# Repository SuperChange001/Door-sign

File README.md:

# Door Sign Design
---
## Preview

## Folder Structure
```bash
├── README.md
├── door-sign
│   ├── bom
│   │   ├── Parts_ordering_digikey.xlsx
│   │   └── ibom.html
│   ├── door-sign.kicad_pcb
│   ├── door-sign.kicad_prl
│   ├── door-sign.kicad_pro
│   ├── door-sign.kicad_sch
│   ├── fp-lib-table
│   ├── schematic.pdf
│   └── sym-lib-table
├── images
│   └── preview.jpg
└── libs
```

## Todo
- [x] schematic
- [x] pcb
- [x] check
- [x] bom
- [x] order
    - [x] pcb
    - [x] components
- [x] test
    - found one error that the direction of the switch is is not as intuative as it should be, and this is fixed in in v1.0
    - found the potentiometer is not in the center of the rectangle, and this is fixed in v1.0
    - add version number to the pcb
- [x] revision for 1.0
    - [x] add version number to the pcb
    - [x] fix the direction of the switch
    - [x] fix the position of the potentiometer

## Acknowledgement
Thanks, Peter (I should add his GitHub account here), for the idea and the perfect layout of the door sign.

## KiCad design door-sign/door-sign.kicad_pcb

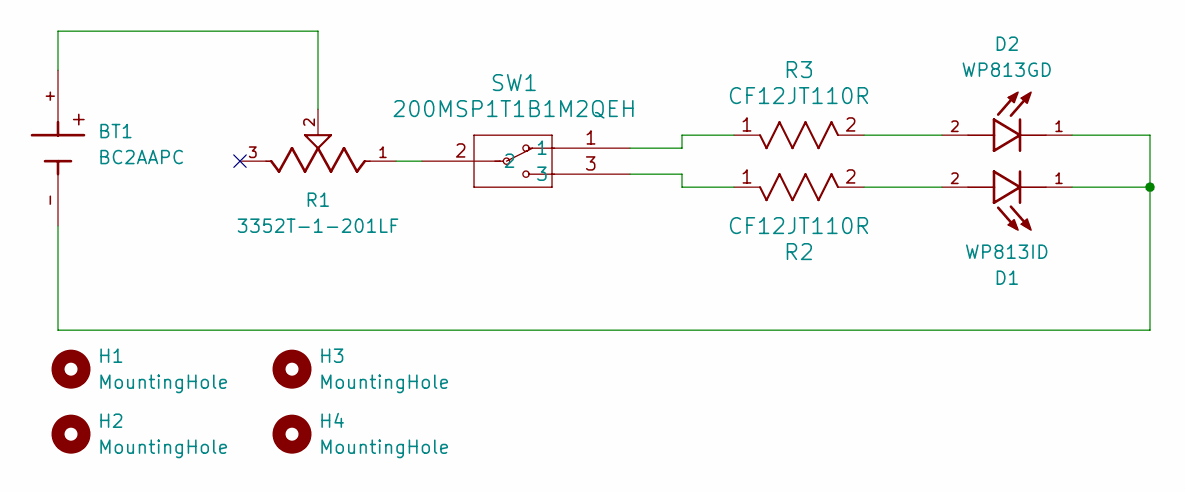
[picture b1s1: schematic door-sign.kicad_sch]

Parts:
BT1: BC2AAPC; BAT_BC2AAPC; PARTREV M
D1: WP813ID; LEDRD254W57D1100H1450; PARTREV V.9B
D2: WP813GD; LEDRD254W57D1100H1450; PARTREV V.9B
H1, H2, H3, H4: MountingHole; MountingHole_5mm
R1: 3352T-1-201LF; TRIM_3352T-1-501LF; PARTREV 08/19
R2, R3: CF12JT110R; STA_CF12_STP
SW1: 200MSP1T1B1M2QEH; 200MSP1T1B1M2QEH_EWI

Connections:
unnamed: BT1.+, R1.2
unnamed: BT1.-, D1.1, D2.1
unnamed: D1.2, R2.2
unnamed: D2.2, R3.2
unnamed: R1.1, SW1.2
unnamed: R2.1, SW1.3
unnamed: R3.1, SW1.1

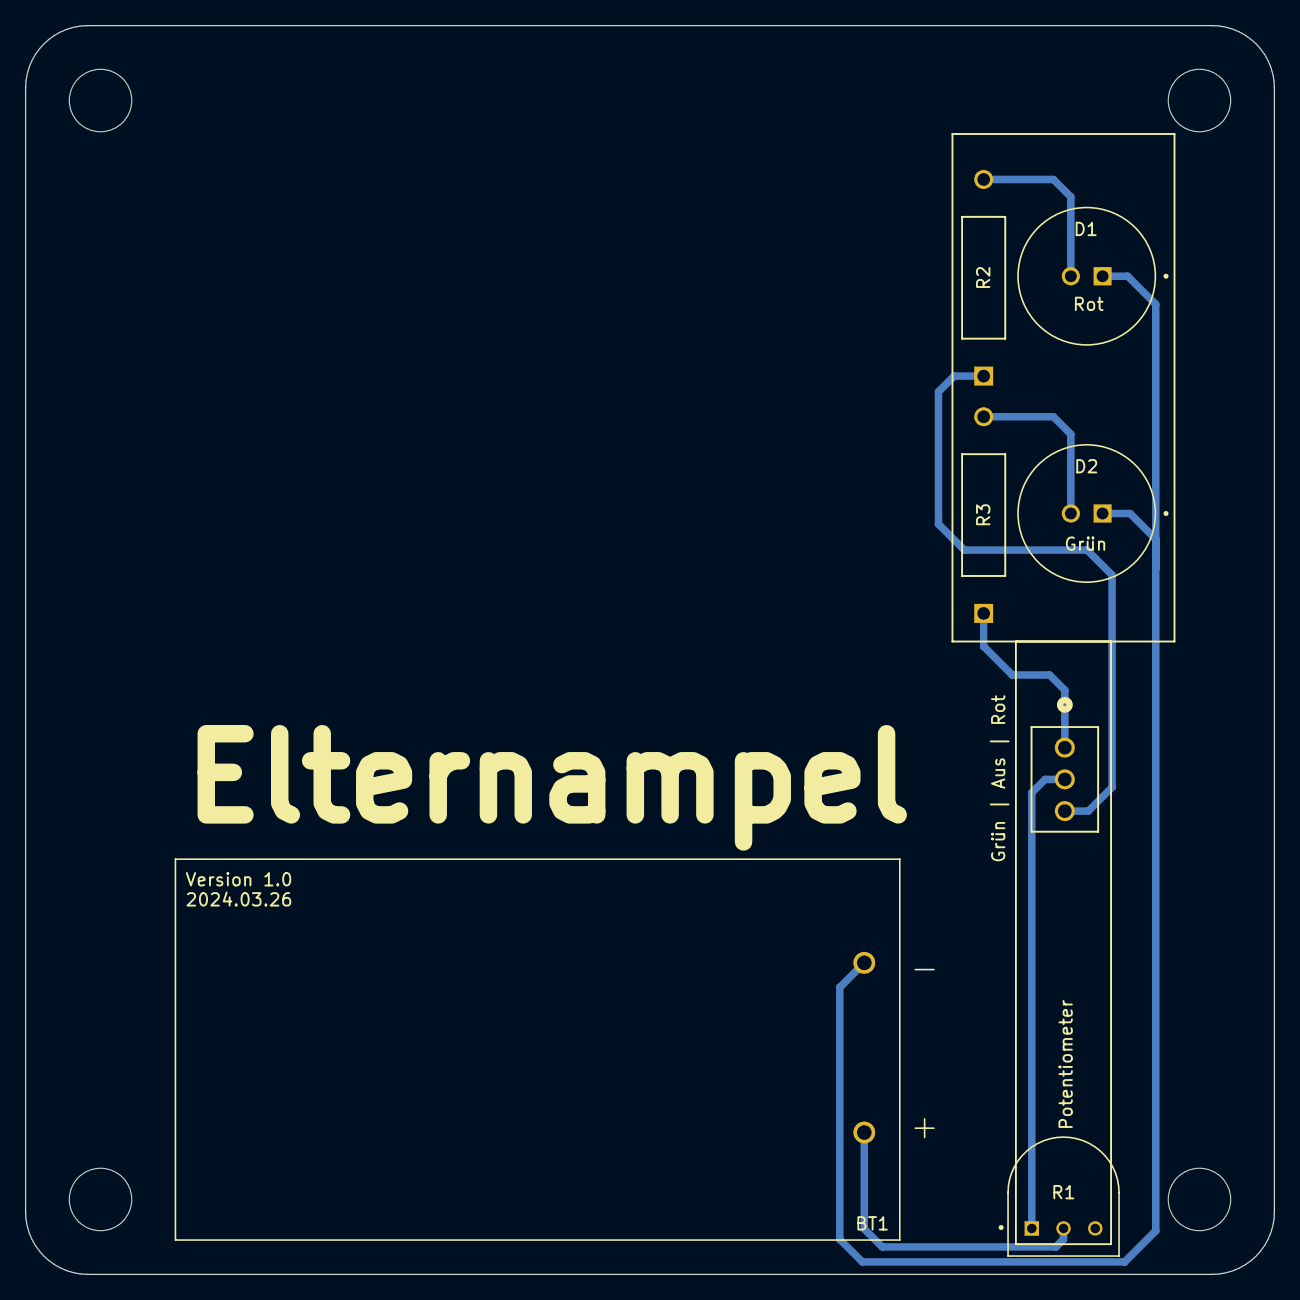
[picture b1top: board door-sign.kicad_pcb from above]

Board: 2 copper layers, 100.0 x 100.0 mm, 11 parts (0 on the bottom side), 7 nets.

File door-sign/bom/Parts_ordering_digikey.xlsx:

Index | Quantity | Part Number | Manufacturer Part Number | Description | Customer Reference | Available | Backorder | Unit Price | Extended Price EUR
1 | 20 | BC2AAPC-ND | BC2AAPC | BATTERY HOLDER AA 2 CELL PC PIN |  | 20 | 0 | 1.28900 | 25.78
2 | 50 | CF12JT100RCT-ND | CF12JT100R | RES 100 OHM 5% 1/2W AXIAL |  | 50 | 0 | 0.03580 | 1.79
3 | 20 | WP813ID-ND | WP813ID | LED RED DIFFUSED 10MM T/H |  | 20 | 0 | 0.23900 | 4.78
4 | 20 | 754-1898-ND | WP813GD | LED GREEN DIFFUSED 10MM T/H |  | 20 | 0 | 0.26200 | 5.24
5 | 20 | EG2447-ND | 200MSP1T1B1M2QEH | SWITCH TOGGLE SPDT 3A 120V |  | 20 | 0 | 2.46200 | 49.24
6 | 20 | 3352T-201LF-ND | 3352T-1-201LF | THUMBWHEEL POT 200 OHM 0.5W TOP |  | 20 | 0 | 2.74200 | 54.84

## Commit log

2024-02-18 middle stage, need a green led
2024-02-19 components done
2024-02-19 add readme
2024-03-02 changed one symbol
2024-03-02 changed one footprint
2024-03-02 changed design
2024-03-02 changed the preview
2024-03-02 add documentation
2024-03-02 erc error free
2024-03-02 done
2024-03-02 update image
2024-03-02 moved parts a little bit
2024-03-02 update preview
2024-03-05 update component values
2024-03-05 update schematic and part list for ordering
2024-03-26 fixed errors
